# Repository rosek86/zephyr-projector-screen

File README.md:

# Matter accessory for projector+screen setup

The repository is an attempt to use nRF52840 dongle as a Matter accessory to turn on/off projector using IR remote, and driving motorized screen up and down. 

Matter accessory firmware is large in flash memory footprint, and it requires additional flash memory which is not available in nRF52840 dongle design. I decided to manufacture small addon, with flash memory and 3 JST sockets as a base for this and similar projects in the future.

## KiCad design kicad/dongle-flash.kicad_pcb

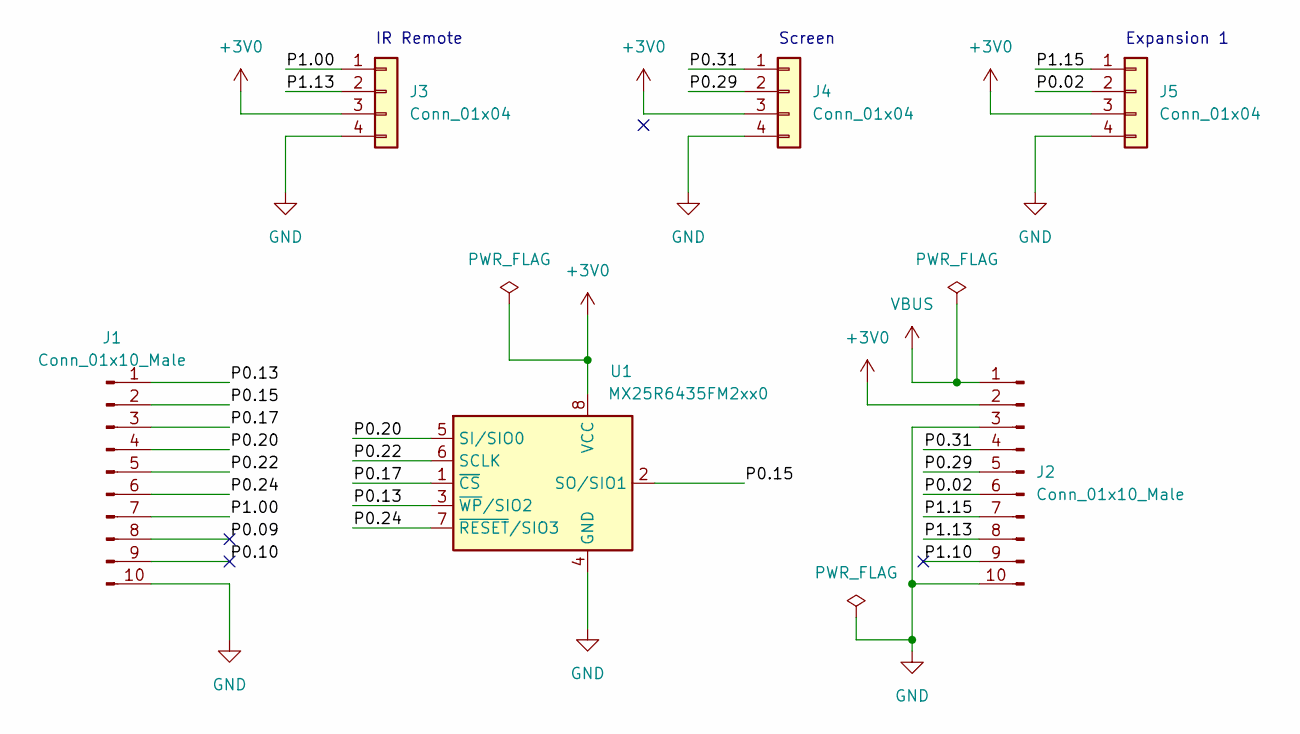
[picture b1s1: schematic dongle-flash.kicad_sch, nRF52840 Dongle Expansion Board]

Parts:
J1, J2: Conn_01x10_Male; PinHeader_1x10_P2.54mm_Vertical
J3, J4, J5: Conn_01x04; JST_SH_BM04B-SRSS-TB_1x04-1MP_P1.00mm_Vertical
U1: MX25R6435FM2xx0; SOIC-8_5.23x5.23mm_P1.27mm

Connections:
+3V0: J2.2, J3.3, J4.3, J5.3, U1.8 (VCC)
/P0.02: J2.6, J5.2
/P0.09: J1.8
/P0.10: J1.9
/P0.13: J1.1, U1.3 (~WP/SIO2)
/P0.15: J1.2, U1.2 (SO/SIO1)
/P0.17: J1.3, U1.1 (~CS)
/P0.20: J1.4, U1.5 (SI/SIO0)
/P0.22: J1.5, U1.6 (SCLK)
/P0.24: J1.6, U1.7 (~RESET/SIO3)
/P0.29: J2.5, J4.2
/P0.31: J2.4, J4.1
/P1.00: J1.7, J3.1
/P1.10: J2.9
/P1.13: J2.8, J3.2
/P1.15: J2.7, J5.1
GND: J1.10, J2.3, J2.10, J3.4, J4.4, J5.4, U1.4 (GND)
VBUS: J2.1

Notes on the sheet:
Expansion 1
Screen
IR Remote

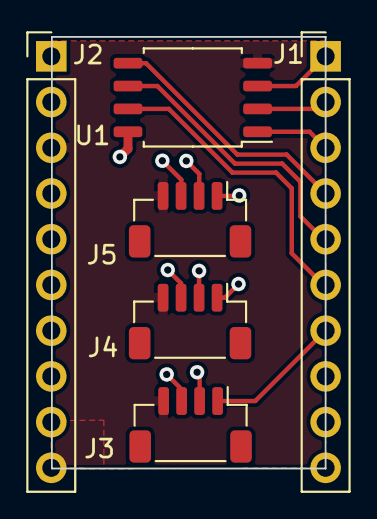
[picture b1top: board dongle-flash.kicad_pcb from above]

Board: 4 copper layers, 15.2 x 24.0 mm, 6 parts (0 on the bottom side), 14 nets.

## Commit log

2023-01-07 add projector functionality to matter example
2023-01-07 add second endpoint for screen, handle screen functionality
2023-01-07 add accessory info
2023-01-07 fix screen driver
2023-01-07 attempt with nrf52840 dongle
2023-01-14 attempt with dongle & soldered flash (still doesn't work)
2023-01-15 working example, dongle with flash built as nRF52840dk
2023-01-18 add custom board, works when built as nrf52840dk, custom board has problem with flash space for mcuboot
2023-01-18 for some reason default board added these two compilation flags, these flags were missing in my custom board - now custom board build works fine
2023-02-04 add kicad design files
2023-02-04 update readme, add image
2023-02-04 update image URL
2023-02-04 update image
2023-02-05 migrate key board configuration from overlay to board
2023-02-05 fix static partition manager, add code to set nrf reg0 voltage
2023-02-05 update kicad project
